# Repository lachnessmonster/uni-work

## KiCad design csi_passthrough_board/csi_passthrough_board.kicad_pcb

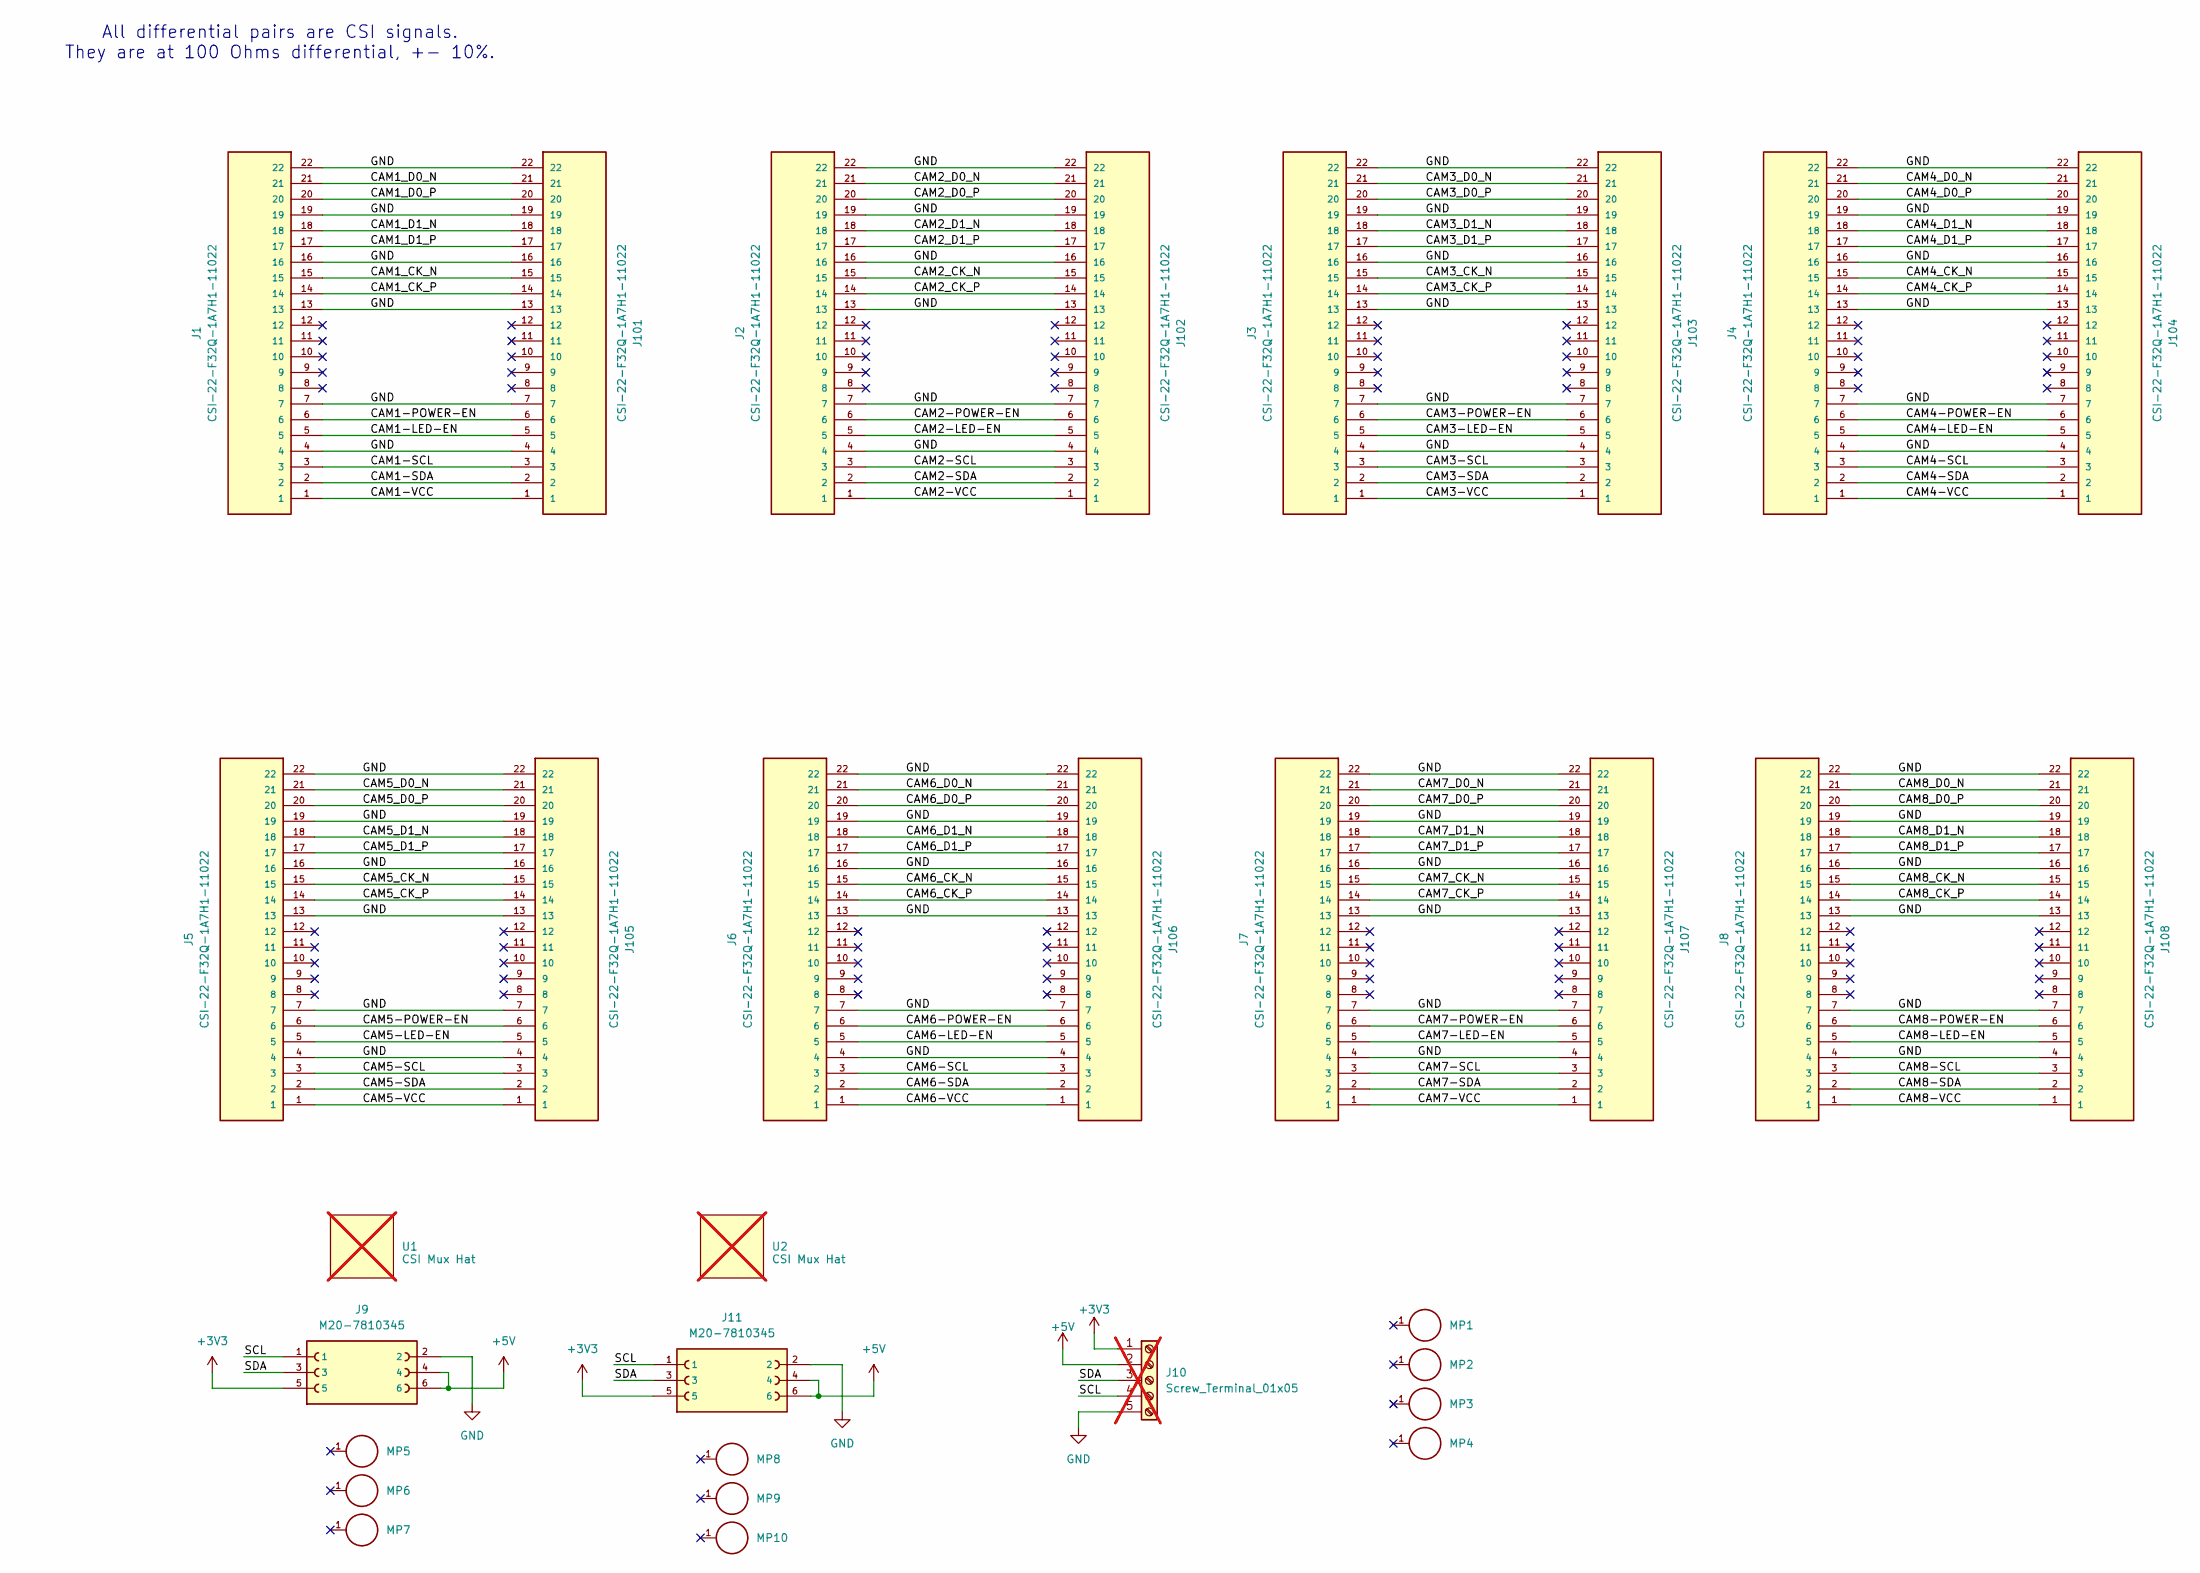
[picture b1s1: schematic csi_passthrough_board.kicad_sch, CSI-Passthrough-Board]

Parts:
J1, J2, J3, J4, J5, J6, J7, J8, J101, J102, J103, J104, J105, J106, J107, J108: CSI-22-F32Q-1A7H1-11022; AMPHENOL_F32Q-1A7H1-11022; PARTREV D; LCSC Part # C3169253
J9, J11: M20-7810345; HARWIN_M20-7810345; LCSC Part # C5666544
J10: Screw_Terminal_01x05; TerminalBlock_Phoenix_MPT-0,5-5-2.54_1x05_P2.54mm_Horizontal; not fitted
MP1, MP2, MP3, MP4: M2.5 x 12mm; WA-SMSI_9774120360; PART-NUMBER 9774040151R; LCSC Part # C22431359
MP5, MP6, MP7, MP8, MP9, MP10: M2.5 x 4mm; WA-SMSI_9774040151; PART-NUMBER 9774040151R; LCSC Part # C5182034
U1, U2: CSI Mux Hat; CSI_Mux_Hat; not fitted

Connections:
+3V3: J9.5, J10.1, J11.5
+5V: J9.4, J9.6, J10.2, J11.4, J11.6
/CAM1-LED-EN: J1.5, J101.5
/CAM1-POWER-EN: J1.6, J101.6
/CAM1-SCL: J1.3, J101.3
/CAM1-SDA: J1.2, J101.2
/CAM1-VCC: J1.1, J101.1
/CAM1_CK_N: J1.15, J101.15
/CAM1_CK_P: J1.14, J101.14
/CAM1_D0_N: J1.21, J101.21
/CAM1_D0_P: J1.20, J101.20
/CAM1_D1_N: J1.18, J101.18
/CAM1_D1_P: J1.17, J101.17
/CAM2-LED-EN: J2.5, J102.5
/CAM2-POWER-EN: J2.6, J102.6
/CAM2-SCL: J2.3, J102.3
/CAM2-SDA: J2.2, J102.2
/CAM2-VCC: J2.1, J102.1
/CAM2_CK_N: J2.15, J102.15
/CAM2_CK_P: J2.14, J102.14
/CAM2_D0_N: J2.21, J102.21
/CAM2_D0_P: J2.20, J102.20
/CAM2_D1_N: J2.18, J102.18
/CAM2_D1_P: J2.17, J102.17
/CAM3-LED-EN: J3.5, J103.5
/CAM3-POWER-EN: J3.6, J103.6
/CAM3-SCL: J3.3, J103.3
/CAM3-SDA: J3.2, J103.2
/CAM3-VCC: J3.1, J103.1
/CAM3_CK_N: J3.15, J103.15
/CAM3_CK_P: J3.14, J103.14
/CAM3_D0_N: J3.21, J103.21
/CAM3_D0_P: J3.20, J103.20
/CAM3_D1_N: J3.18, J103.18
/CAM3_D1_P: J3.17, J103.17
/CAM4-LED-EN: J4.5, J104.5
/CAM4-POWER-EN: J4.6, J104.6
/CAM4-SCL: J4.3, J104.3
/CAM4-SDA: J4.2, J104.2
/CAM4-VCC: J4.1, J104.1
/CAM4_CK_N: J4.15, J104.15
/CAM4_CK_P: J4.14, J104.14
/CAM4_D0_N: J4.21, J104.21
/CAM4_D0_P: J4.20, J104.20
/CAM4_D1_N: J4.18, J104.18
/CAM4_D1_P: J4.17, J104.17
/CAM5-LED-EN: J5.5, J105.5
/CAM5-POWER-EN: J5.6, J105.6
/CAM5-SCL: J5.3, J105.3
/CAM5-SDA: J5.2, J105.2
/CAM5-VCC: J5.1, J105.1
/CAM5_CK_N: J5.15, J105.15
/CAM5_CK_P: J5.14, J105.14
/CAM5_D0_N: J5.21, J105.21
/CAM5_D0_P: J5.20, J105.20
/CAM5_D1_N: J5.18, J105.18
/CAM5_D1_P: J5.17, J105.17
/CAM6-LED-EN: J6.5, J106.5
/CAM6-POWER-EN: J6.6, J106.6
/CAM6-SCL: J6.3, J106.3
/CAM6-SDA: J6.2, J106.2
/CAM6-VCC: J6.1, J106.1
/CAM6_CK_N: J6.15, J106.15
/CAM6_CK_P: J6.14, J106.14
/CAM6_D0_N: J6.21, J106.21
/CAM6_D0_P: J6.20, J106.20
/CAM6_D1_N: J6.18, J106.18
/CAM6_D1_P: J6.17, J106.17
/CAM7-LED-EN: J7.5, J107.5
/CAM7-POWER-EN: J7.6, J107.6
/CAM7-SCL: J7.3, J107.3
/CAM7-SDA: J7.2, J107.2
/CAM7-VCC: J7.1, J107.1
/CAM7_CK_N: J7.15, J107.15
/CAM7_CK_P: J7.14, J107.14
/CAM7_D0_N: J7.21, J107.21
/CAM7_D0_P: J7.20, J107.20
/CAM7_D1_N: J7.18, J107.18
/CAM7_D1_P: J7.17, J107.17
/CAM8-LED-EN: J8.5, J108.5
/CAM8-POWER-EN: J8.6, J108.6
/CAM8-SCL: J8.3, J108.3
/CAM8-SDA: J8.2, J108.2
/CAM8-VCC: J8.1, J108.1
/CAM8_CK_N: J8.15, J108.15
/CAM8_CK_P: J8.14, J108.14
/CAM8_D0_N: J8.21, J108.21
/CAM8_D0_P: J8.20, J108.20
/CAM8_D1_N: J8.18, J108.18
/CAM8_D1_P: J8.17, J108.17
/SCL: J9.1, J10.4, J11.1
/SDA: J9.3, J10.3, J11.3
GND: J1.4, J1.7, J1.13, J1.16, J1.19, J1.22, J2.4, J2.7, J2.13, J2.16, J2.19, J2.22, J3.4, J3.7, J3.13, J3.16, J3.19, J3.22, J4.4, J4.7, J4.13, J4.16, J4.19, J4.22, J5.4, J5.7, J5.13, J5.16, J5.19, J5.22, J6.4, J6.7, J6.13, J6.16, J6.19, J6.22, J7.4, J7.7, J7.13, J7.16, J7.19, J7.22, J8.4, J8.7, J8.13, J8.16, J8.19, J8.22, J9.2, J10.5, J11.2, J101.4, J101.7, J101.13, J101.16, J101.19, J101.22, J102.4, J102.7, J102.13, J102.16, J102.19, J102.22, J103.4, J103.7, J103.13, J103.16, J103.19, J103.22, J104.4, J104.7, J104.13, J104.16, J104.19, J104.22, J105.4, J105.7, J105.13, J105.16, J105.19, J105.22, J106.4, J106.7, J106.13, J106.16, J106.19, J106.22, J107.4, J107.7, J107.13, J107.16, J107.19, J107.22, J108.4, J108.7, J108.13, J108.16, J108.19, J108.22

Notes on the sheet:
All differential pairs are CSI signals. They are at 100 Ohms differential, +- 10%.

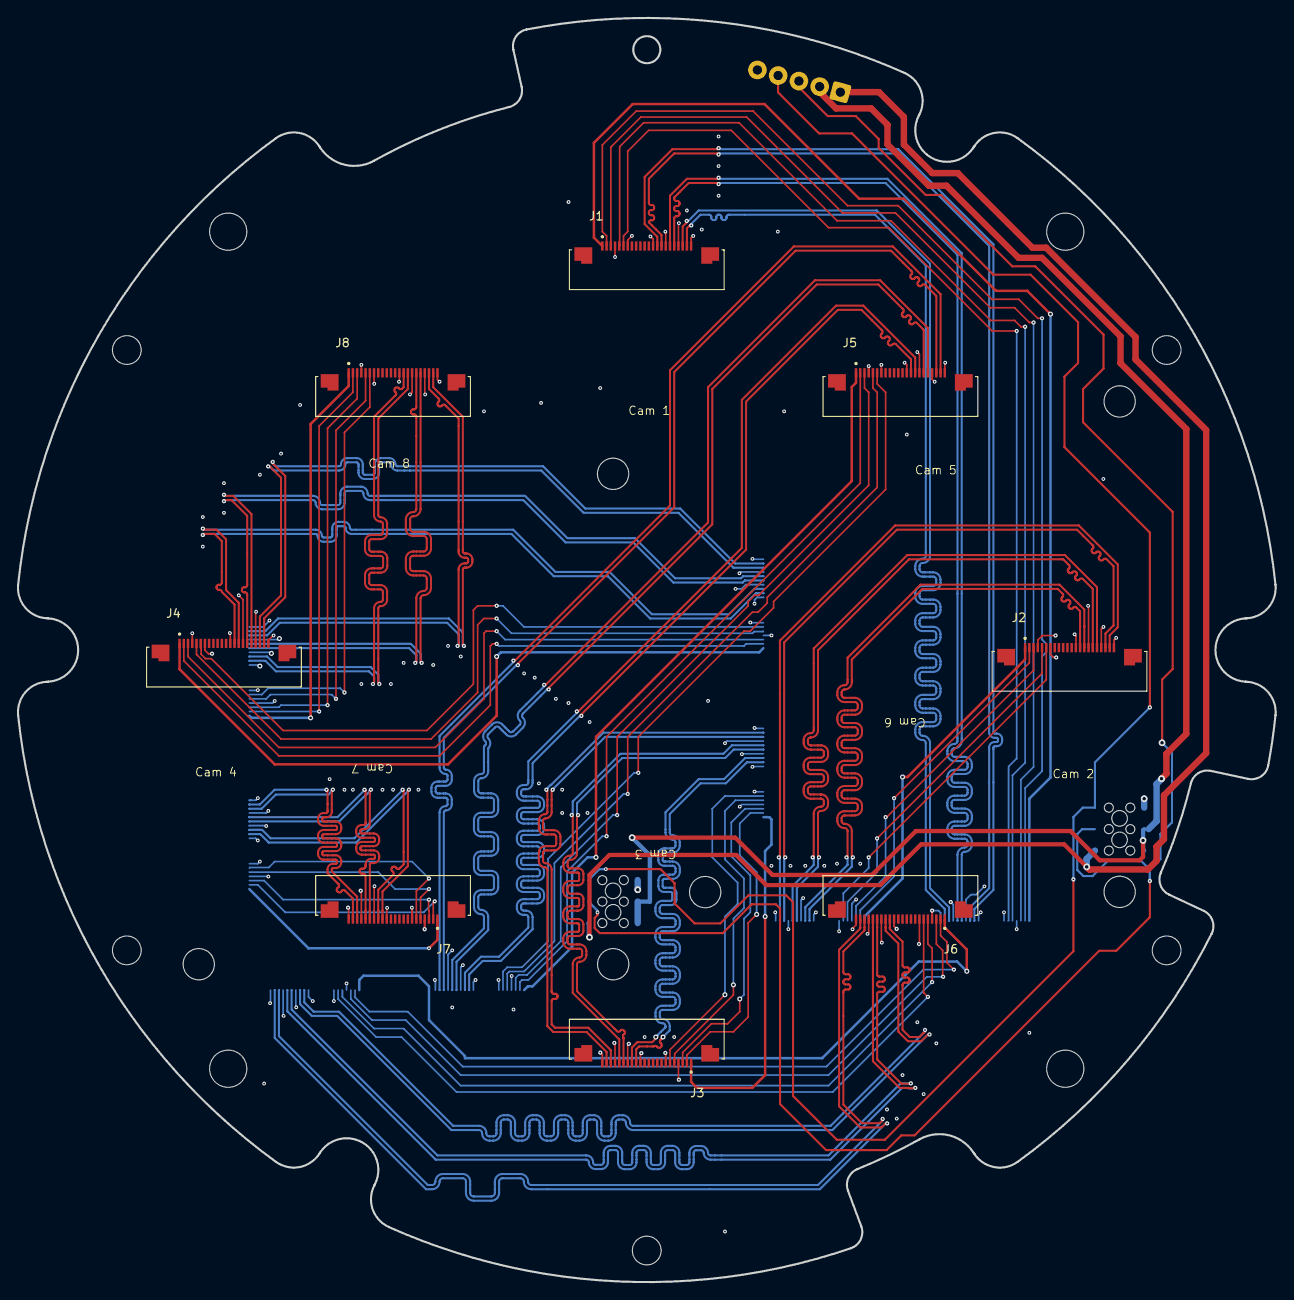
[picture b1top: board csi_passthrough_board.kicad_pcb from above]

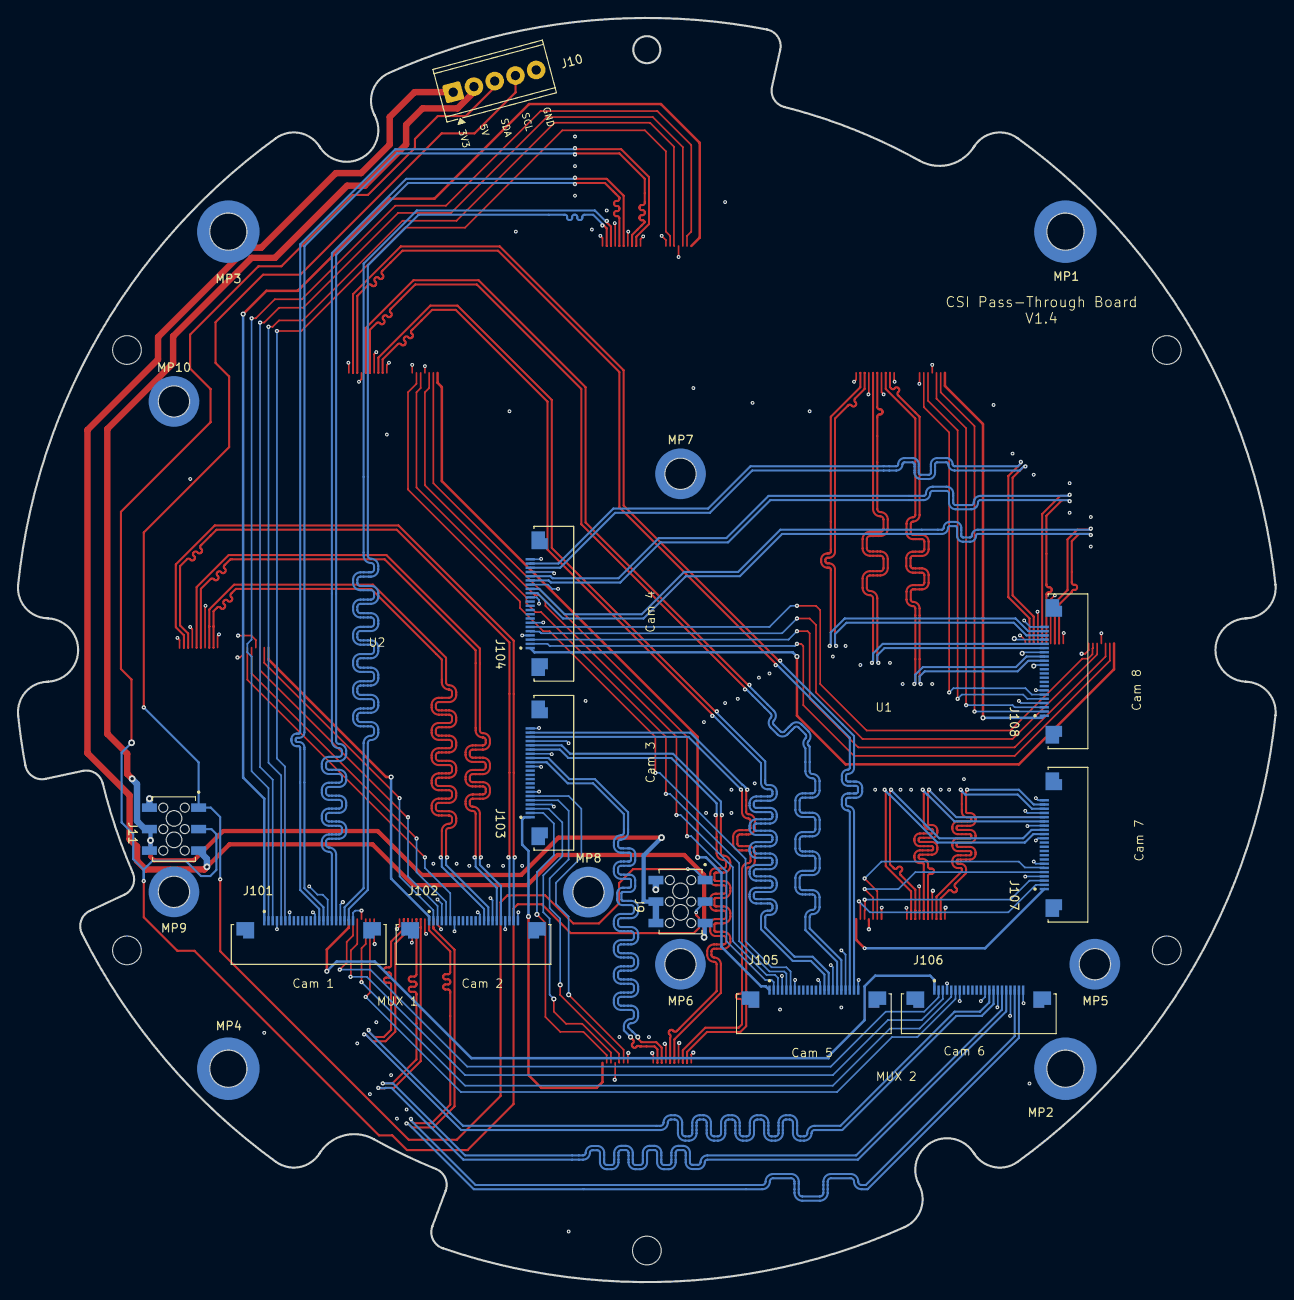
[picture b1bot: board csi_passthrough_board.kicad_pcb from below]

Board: 4 copper layers, 148.7 x 149.5 mm, 31 parts (23 on the bottom side), 93 nets.

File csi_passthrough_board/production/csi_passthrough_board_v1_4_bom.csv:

Designator,Footprint,Quantity,Value,LCSC Part #
"J1, J101, J102, J103, J104, J105, J106, J107, J108, J2, J3, J4, J5, J6, J7, J8",AMPHENOL_F32Q-1A7H1-11022,16,CSI-22-F32Q-1A7H1-11022,C3169253
"J11, J9",HARWIN_M20-7810345,2,M20-7810345,C5666544
"MP1, MP2, MP3, MP4",WA-SMSI_9774120360,4,M2.5 x 12mm,C22431359
"MP10, MP5, MP6, MP7, MP8, MP9",WA-SMSI_9774040151,6,M2.5 x 4mm,C5182034

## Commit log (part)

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2026-06-29 gitignore
2026-06-29 final 1
2026-06-29 reorganised
2026-06-29 Add files via upload
    adding original passthrough
2026-06-29 removing files
2026-06-29 remove
2026-06-30 after standoffs, before shifting
